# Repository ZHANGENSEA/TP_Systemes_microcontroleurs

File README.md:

# TP_Systemes_microcontroleurs

1.1.6 Activez l’USART2 en mode Asynchrone. Gardez les paramètres par défaut, et
notez le baud rate.

Réponse : 115200 BITS/S

1.2.13 Pourquoi PB9 est relié à la masse ? 

Réponse : 

PB9 n’est pas relié directement à la masse. Elle est reliée à la masse à travers une résistance pull down. Elle fonctionne comme une résistance de tirage (vers le bas). Son rôle est de s'assurer que la broche reste à un niveau logique bas (0V) lorsque rien n'est connecté à celle-ci ou si le dispositif connecté est en haute impédance. Cela évite que la broche flotte, ce qui pourrait mener à des états logiques indéfinis et à une consommation de courant inutile due aux oscillations de la tension. 

De plus si PB9 est utilisée comme entrée, la résistance permet à la broche de détecter un niveau bas jusqu'à ce qu'elle soit intentionnellement mise à un niveau haut par un autre circuit.  

La valeur élevée de la résistance (100k ohms) assure qu'il y a une très faible consommation de courant à travers la résistance lorsque la broche est mise à un niveau haut par le microcontrôleur ou un autre circuit. Cette configuration permet donc d'économiser de l'énergie et de prévenir un état indéfini sans interférer avec les signaux actifs. 

1.2.14 Quel est le rôle de L1, C5 et C7 ? 

Réponse : 

C5 et C7 sont des condensateurs de découplage et L1 joue le rôle de filtre 

L1 forme une barrière contre le bruit de haute fréquence tandis que C7 aide à court-circuiter ce bruit vers la masse, l'éliminant ainsi du système. C5 agit comme un réservoir d'énergie pour gérer les besoins en courant plus lent et plus large de la puce. Cette combinaison permet de filtrer une large gamme de fréquences de bruit et assurer une alimentation propre et stable pour le microcontrôleur. 

1.3.3 Quelle page de la datasheet indique les valeurs des condensateurs ? 

Réponse :  Page 3 du datasheet “buxxsd5wg-e”. (voir fichier word pour capture)

1.3.5 Quelle page de la datasheet nous indique les valeurs de condensateurs ? 

Réponse : Page 15 du datasheet “22244B-54643” (voir fichier word pour capture)

1.3.6 Quel est le rôle de la broche CS?  

Réponse :  La broche CS est utilisée pour activer et désactiver le dispositif DAC. Lorsque la broche CS est mise à bas (niveau logique 0), le DAC est sélectionné et peut communiquer avec le microcontrôleur. Lorsque CS est à haut (niveau logique 1), le DAC ignore les signaux du bus SPI, permettant ainsi à d'autres dispositifs sur le même bus SPI de communiquer sans interférence.  

1.3.7 Quel est le rôle de la broche LDAC ?  

Réponse : La broche LDAC est utilisée pour contrôler le moment où la sortie du DAC est mise à jour. Dans certains DACs, il est possible d’écrire dans un premier temps la donnée numérique dans un registre interne, puis, en mettant la broche LDAC à bas, d'indiquer au DAC de mettre à jour la sortie analogique avec la valeur stockée dans ce registre. 

1.3.8 Pourquoi le signal MISO n’est pas utilisé ? 

Réponse : Le signal MISO n'est pas utilisé dans ce cas car le MCP4801 est un DAC unidirectionnel qui ne nécessite que des données entrantes du microcontrôleur pour définir le niveau de tension de sortie. Il n'y a pas de nécessité pour le DAC d'envoyer des données en retour au microcontrôleur, d'où l'absence de connexion MISO dans ce cas. Le bus SPI est donc utilisé en mode unidirectionnel ici, seulement pour envoyer des données au DAC. 

1.3.10 Où trouve-t-on les indications du pinout du connecteur SWD ? 

Réponse :  Les indications sont trouvables sur le lien suivant :  

https://stm32-base.org/guides/connecting-your-debugger.html (voir word pour capture

1.4.3 Que signifie 0805 ? 0603 ? 1206 ?  

Réponse :  Les chiffres 0805, 0603 et 1206 font référence à des tailles standard de composants électroniques en montage en surface (SMD, pour Surface-Mount Device). Ces chiffres indiquent les dimensions du composant : 0603 désigne un composant qui mesure environ 0.06 pouces x 0.03 pouces, soit 1.6 mm x 0.8 mm. 

0805 désigne un composant qui mesure environ 0.08 pouces x 0.05 pouces, soit 2.0 mm x 1.25 mm. 

1206 désigne un composant qui mesure environ 0.12 pouces x 0.06 pouces, soit 3.0 mm x 1.5 mm. 

1.4.4 Que signifie LQFP ? SOT-223 ? SOIC ? Ne vous contentez pas de donner le sigle, j’attends une petite description (vous pouvez copier-coller depuis wikipedia, mais lisez avant quand même)) 

Réponse :   

LQFP (Low-profile Quad Flat Package) : Il s'agit d'un type de boîtier plat rectangulaire avec des connexions sur les quatre côtés. Il est conçu pour occuper peu d'espace en hauteur (d'où le terme "low-profile") et offre une bonne efficacité pour la dissipation thermique. Les broches sortent des côtés du composant et se replient sous le boîtier, ce qui permet un montage en surface sur un circuit imprimé. 

SOT-223 (Small Outline Transistor-223) : C'est un type de boîtier pour les composants à semi-conducteurs qui est plus grand que le traditionnel SOT-23, offrant une meilleure capacité de dissipation de chaleur. Le boîtier SOT-223 a généralement trois broches et une grande languette métallique à l'arrière qui sert à la fois de broche électrique supplémentaire et de dissipateur thermique. 

SOIC (Small Outline Integrated Circuit) : C'est un type de boîtier à montage en surface utilisé pour les circuits intégrés. Il a des broches sur les deux côtés et est plus étroit que le boîtier DIP (Dual In-line Package) traditionnel. 

3.1.4 Que signifie __STATIC_INLINE ?

Réponse :

__STATIC_INLINE permet d'indiquer au compilateur de remplacer les appels de la fonction par le contenu de la fonction (similaire à une fonction macro)

3.1.5 Et pourquoi y a-t-il du code dans un .h alors que Môssieur Fiack vous a expres-
sément demandé de pas le faire ? (Les deux questions sont peut-être liés, va
savoir)

Réponse : Si c'est une fonction INLINE dans un header, elle est copiée dans le fichier source.

3.2.2 

Quelle valeur donner au prescaler ?

Réponse :

On donne 64 au prescaler car 16 Mhz/64 = 250 kHz. On obtient une période de 255 pour le compteur du timer et 1 khz pour le PWR.

3.3.3 Quelles sont les valeurs de PSC et de ARR ?

Réponse : 

On sait que la fréquence du processeur est de 16 MHz. Et on souhaite un timer qui déclenche une interruption toutes les milli-secondes, donc avec une fréquence de 1 khz. On règle donc le PSC à 250 et l'ARR à 64 pour avoir 1 kHz.

3.3.6 Où se situe la routine de service d’interruption ?

Réponse :

Elle se situe dans "stm3210xx_it.c"

3.3.7 Que manque-t-il par rapport au code généré par la HAL ?

Réponse:

La désactivation du flag d'interruption

3.3.8 En quoi est-ce catastrophique ?

Réponse :

L'interruption va être lancée en boucle

3.3.9 Que faire ?

Réponse :

Ecrire le flag dans la routine d'interruption

3.4.5 Une erreur s’est glissée dans le code précédent, saurez-vous la retrouver ?

Réponse : 

Il faut rajouter un & dans la ligne SerialTransmit(&ch,1);
Il est nécessaire de passer un pointeur sur le char.

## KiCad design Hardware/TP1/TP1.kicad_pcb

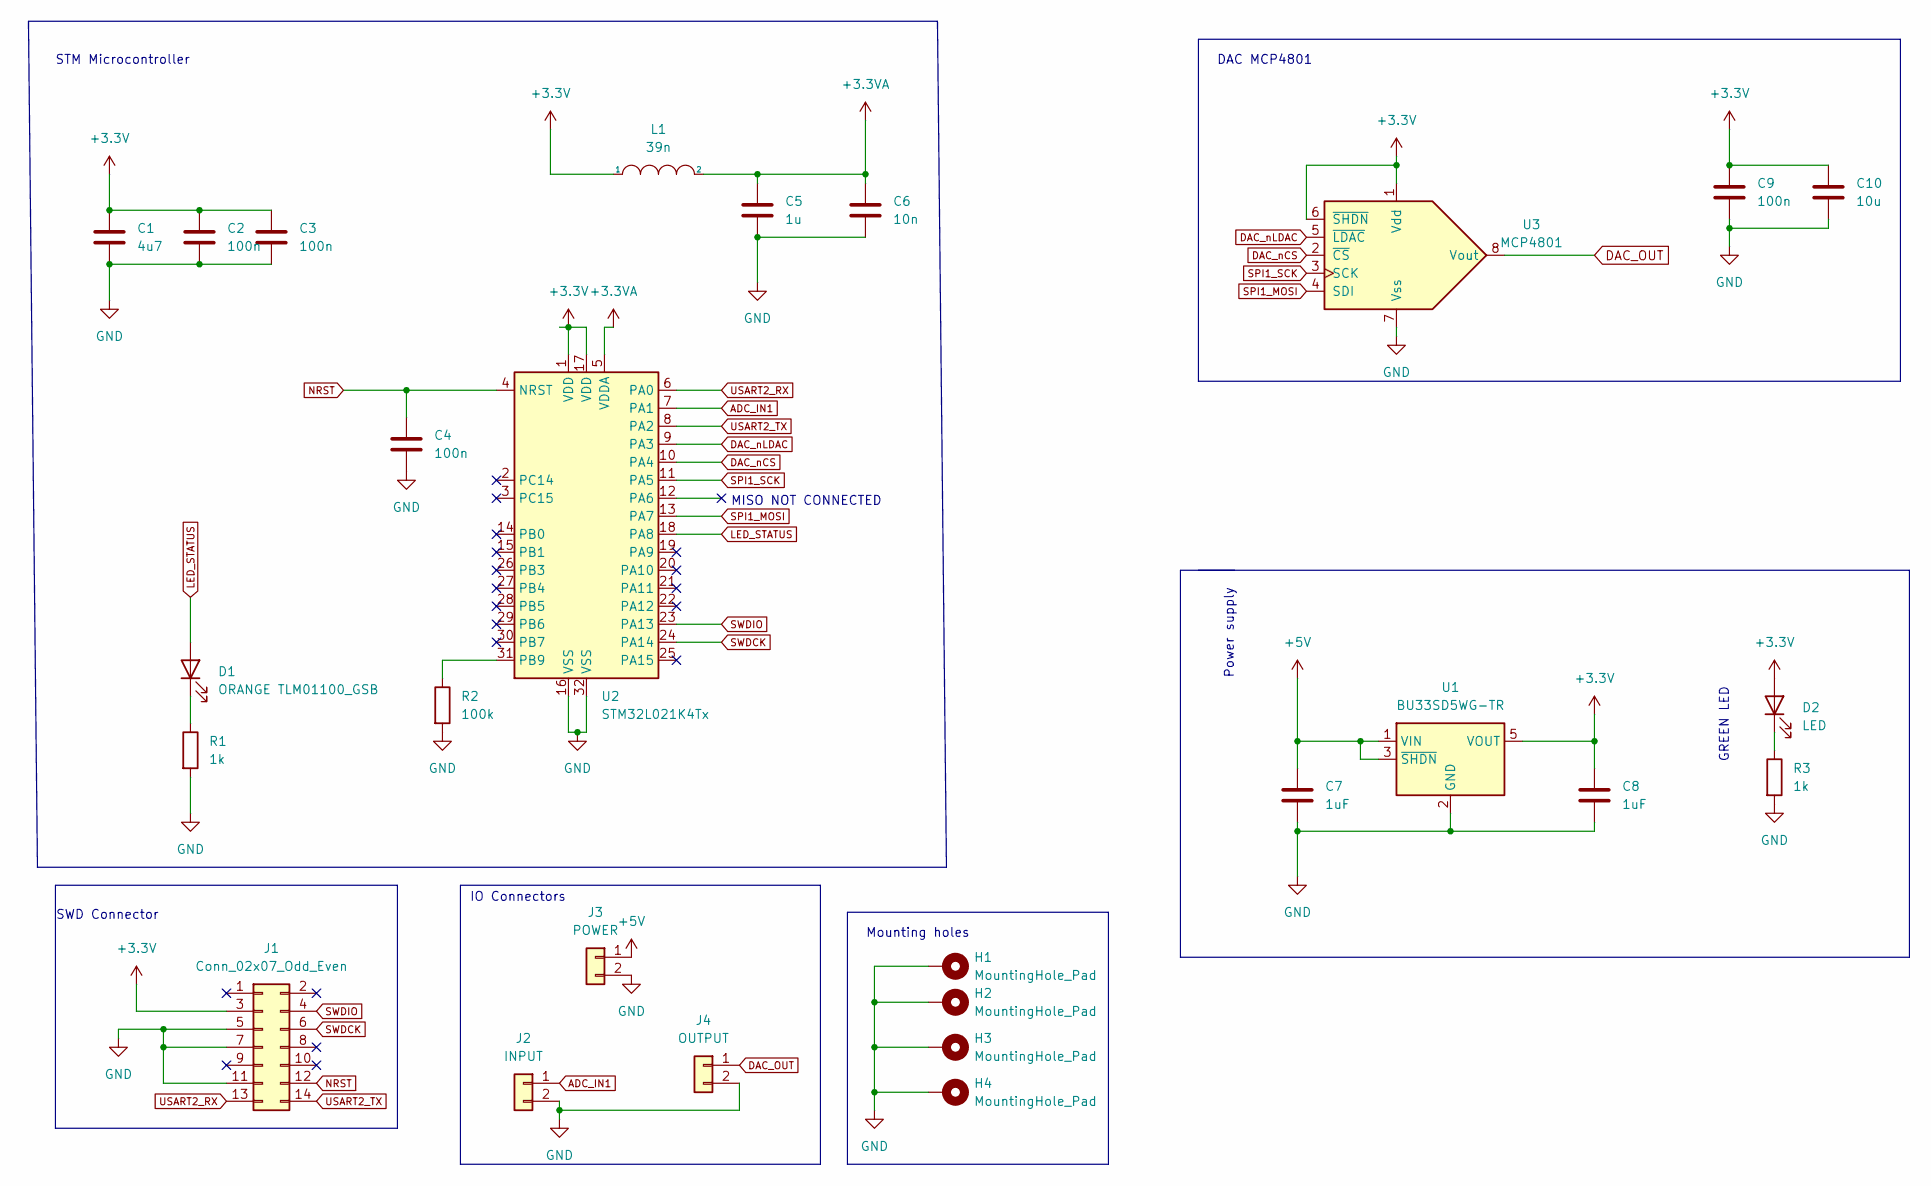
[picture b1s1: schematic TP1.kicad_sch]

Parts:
C1: 4u7; C_0805_2012Metric_Pad1.18x1.45mm_HandSolder
C2, C3, C4, C9: 100n; C_0805_2012Metric_Pad1.18x1.45mm_HandSolder
C5: 1u; C_0805_2012Metric_Pad1.18x1.45mm_HandSolder
C6: 10n; C_0805_2012Metric_Pad1.18x1.45mm_HandSolder
C7, C8: 1uF; C_0805_2012Metric
C10: 10u; C_0805_2012Metric
D1: ORANGE TLM01100_GSB; LED_0603_1608Metric_Pad1.05x0.95mm_HandSolder
D2: LED; LED_0603_1608Metric_Pad1.05x0.95mm_HandSolder
H1, H2, H3, H4: MountingHole_Pad; MountingHole_3.2mm_M3_Pad
J1: Conn_02x07_Odd_Even; PinHeader_2x07_P1.27mm_Vertical_SMD
J2: INPUT; JST_XH_B2B-XH-A_1x02_P2.50mm_Vertical
J3: POWER; JST_XH_B2B-XH-A_1x02_P2.50mm_Vertical
J4: OUTPUT; JST_XH_B2B-XH-A_1x02_P2.50mm_Vertical
L1: 39n; L_0805_2012Metric_Pad1.05x1.20mm_HandSolder
R1, R3: 1k; R_0805_2012Metric_Pad1.20x1.40mm_HandSolder
R2: 100k; R_0805_2012Metric_Pad1.20x1.40mm_HandSolder
U1: BU33SD5WG-TR; SOT-23-5
U2: STM32L021K4Tx; LQFP-32_7x7mm_P0.8mm
U3: MCP4801; SOIC-8_3.9x4.9mm_P1.27mm

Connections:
+3.3V: C1.1, C2.1, C3.1, C8.1, C9.1, C10.1, D2.2 (A), J1.3, L1.1, U1.5 (VOUT), U2.1 (VDD), U2.17 (VDD), U3.1 (Vdd), U3.6 (~SHDN)
+3.3VA: C5.1, C6.1, L1.2, U2.5 (VDDA)
+5V: C7.1, J3.1, U1.1 (VIN), U1.3 (~SHDN)
ADC_IN1: J2.1, U2.7 (PA1)
DAC_OUT: J4.1, U3.8 (Vout)
DAC_nCS: U2.10 (PA4), U3.2 (~CS)
DAC_nLDAC: U2.9 (PA3), U3.5 (~LDAC)
GND: C1.2, C2.2, C3.2, C4.2, C5.2, C6.2, C7.2, C8.2, C9.2, C10.2, H1.1, H2.1, H3.1, H4.1, J1.5, J1.7, J1.11, J2.2, J3.2, J4.2, R1.2, R2.2, R3.2, U1.2 (GND), U2.16 (VSS), U2.32 (VSS), U3.7 (Vss)
LED_STATUS: D1.2 (A), U2.18 (PA8)
NRST: C4.1, J1.12, U2.4 (NRST)
unnamed: D1.1 (K), R1.1
unnamed: D2.1 (K), R3.1
unnamed: R2.1, U2.31 (PB9)
SPI1_MOSI: U2.13 (PA7), U3.4 (SDI)
SPI1_SCK: U2.11 (PA5), U3.3 (SCK)
SWDCK: J1.6, U2.24 (PA14)
SWDIO: J1.4, U2.23 (PA13)
USART2_RX: J1.13, U2.6 (PA0)
USART2_TX: J1.14, U2.8 (PA2)

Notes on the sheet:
Mounting holes
SWD Connector
DAC MCP4801
Power supply
STM Microcontroller
MISO NOT CONNECTED
IO Connectors
GREEN LED

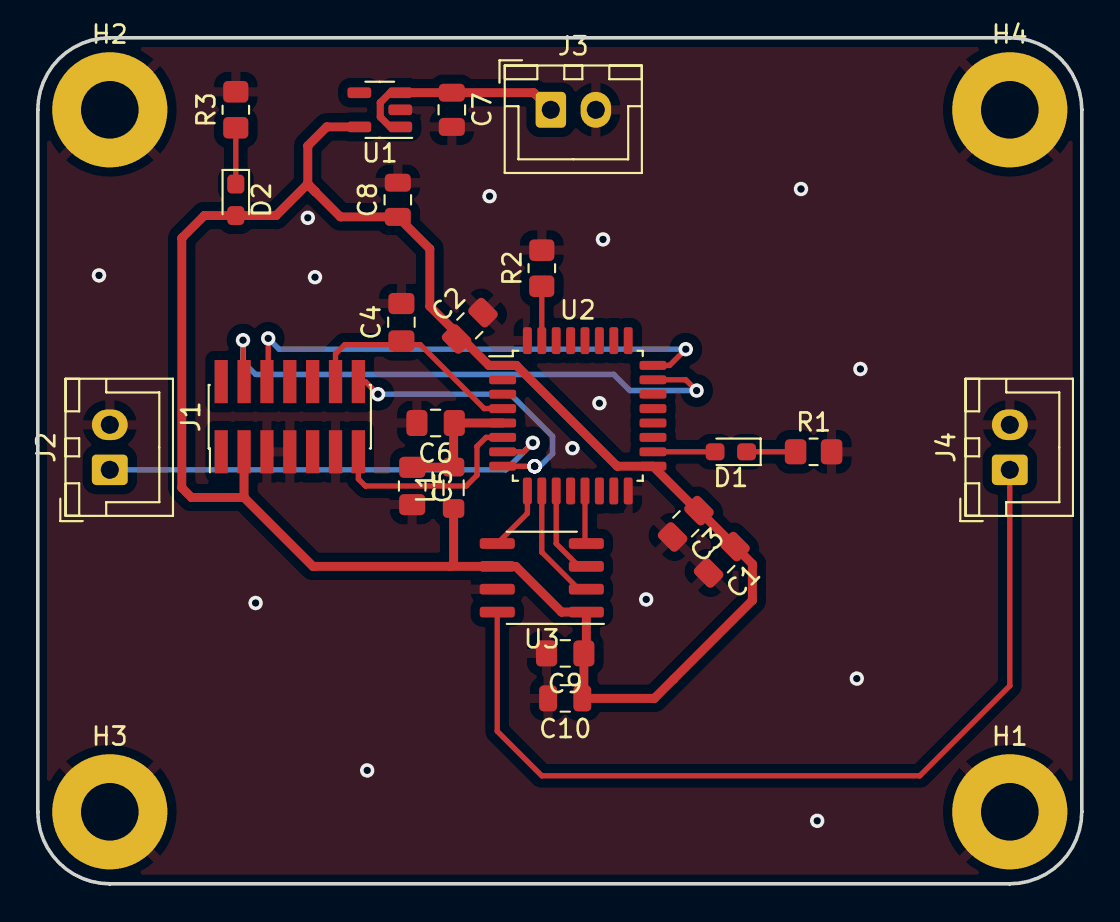
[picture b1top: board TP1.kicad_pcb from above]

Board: 2 copper layers, 58.0 x 47.0 mm, 27 parts (0 on the bottom side), 19 nets.

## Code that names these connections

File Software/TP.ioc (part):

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Mcu.Name=STM32L021K4Tx
Mcu.Package=LQFP32
Mcu.UserName=STM32L021K4Tx
PA0-CK_IN.Mode=Asynchronous
PA0-CK_IN.Signal=USART2_RX
PA1.Mode=IN1
PA1.Signal=ADC_IN1
PA13.Mode=Serial_Wire
PA13.Signal=SYS_SWDIO
PA14.Mode=Serial_Wire
PA14.Signal=SYS_SWCLK
PA2.Mode=Asynchronous
PA2.Signal=USART2_TX
PA3.Signal=GPIO_Output
PA4.GPIOParameters=GPIO_Label
PA4.GPIO_Label=DAC_nCS
PA4.Signal=GPIO_Output
PA5.Mode=Simplex_Bidirectional_Master
PA5.Signal=SPI1_SCK
PA7.Mode=Simplex_Bidirectional_Master
PA7.Signal=SPI1_MOSI
PA8.Signal=S_TIM2_CH1
RCC.HSE_VALUE=8000000
RCC.SYSCLKFreq_VALUE=16000000
RCC.SYSCLKSource=RCC_SYSCLKSOURCE_PLLCLK
board=custom

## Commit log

2024-02-04 First!
2024-02-26 Create 1
2024-02-26 Create 2
2024-02-26 Create 3
2024-02-27 datasheet
2024-02-29 kicad
